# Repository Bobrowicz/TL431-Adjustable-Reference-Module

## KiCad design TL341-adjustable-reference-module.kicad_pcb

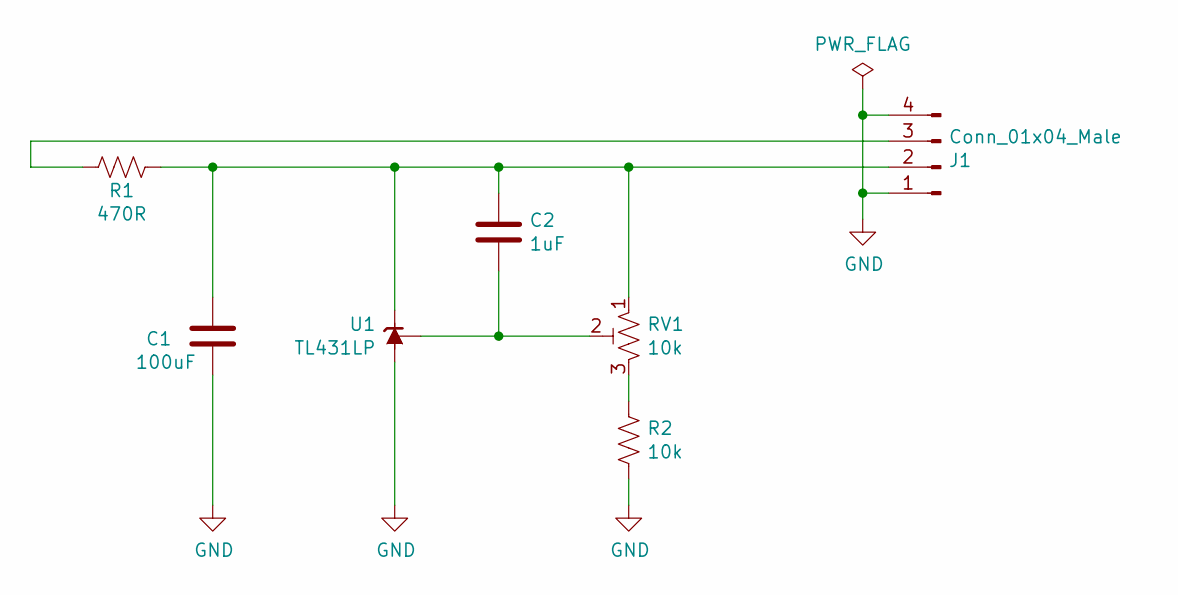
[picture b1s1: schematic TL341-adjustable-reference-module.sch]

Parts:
C1: 100uF; C_2220_HandSoldering
C2: 1uF; C_0805_HandSoldering
J1: Conn_01x04_Male; PinHeader_1x04_P2.54mm_Vertical
R1: 470R; R_0805_HandSoldering
R2: 10k; R_0805_HandSoldering
RV1: 10k; Potentiometer_Trimmer_Bourns_3266W
U1: TL431LP; TO-92_Inline_Narrow_Oval

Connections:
GND: C1.2, J1.1, J1.4, R2.1, U1.2 (A)
unnamed: C1.1, C2.1, J1.2, R1.1, RV1.1, U1.3 (K)
unnamed: C2.2, RV1.2, U1.1 (REF)
unnamed: J1.3, R1.2
unnamed: R2.2, RV1.3

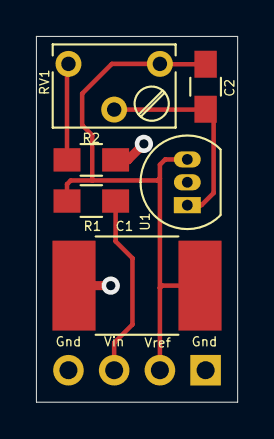
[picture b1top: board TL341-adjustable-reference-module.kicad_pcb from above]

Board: 2 copper layers, 11.2 x 20.3 mm, 7 parts (1 on the bottom side), 5 nets.

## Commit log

2021-02-20 Complete
2021-02-23 Silk screen edits
2021-04-16 removed fp-info-cache
